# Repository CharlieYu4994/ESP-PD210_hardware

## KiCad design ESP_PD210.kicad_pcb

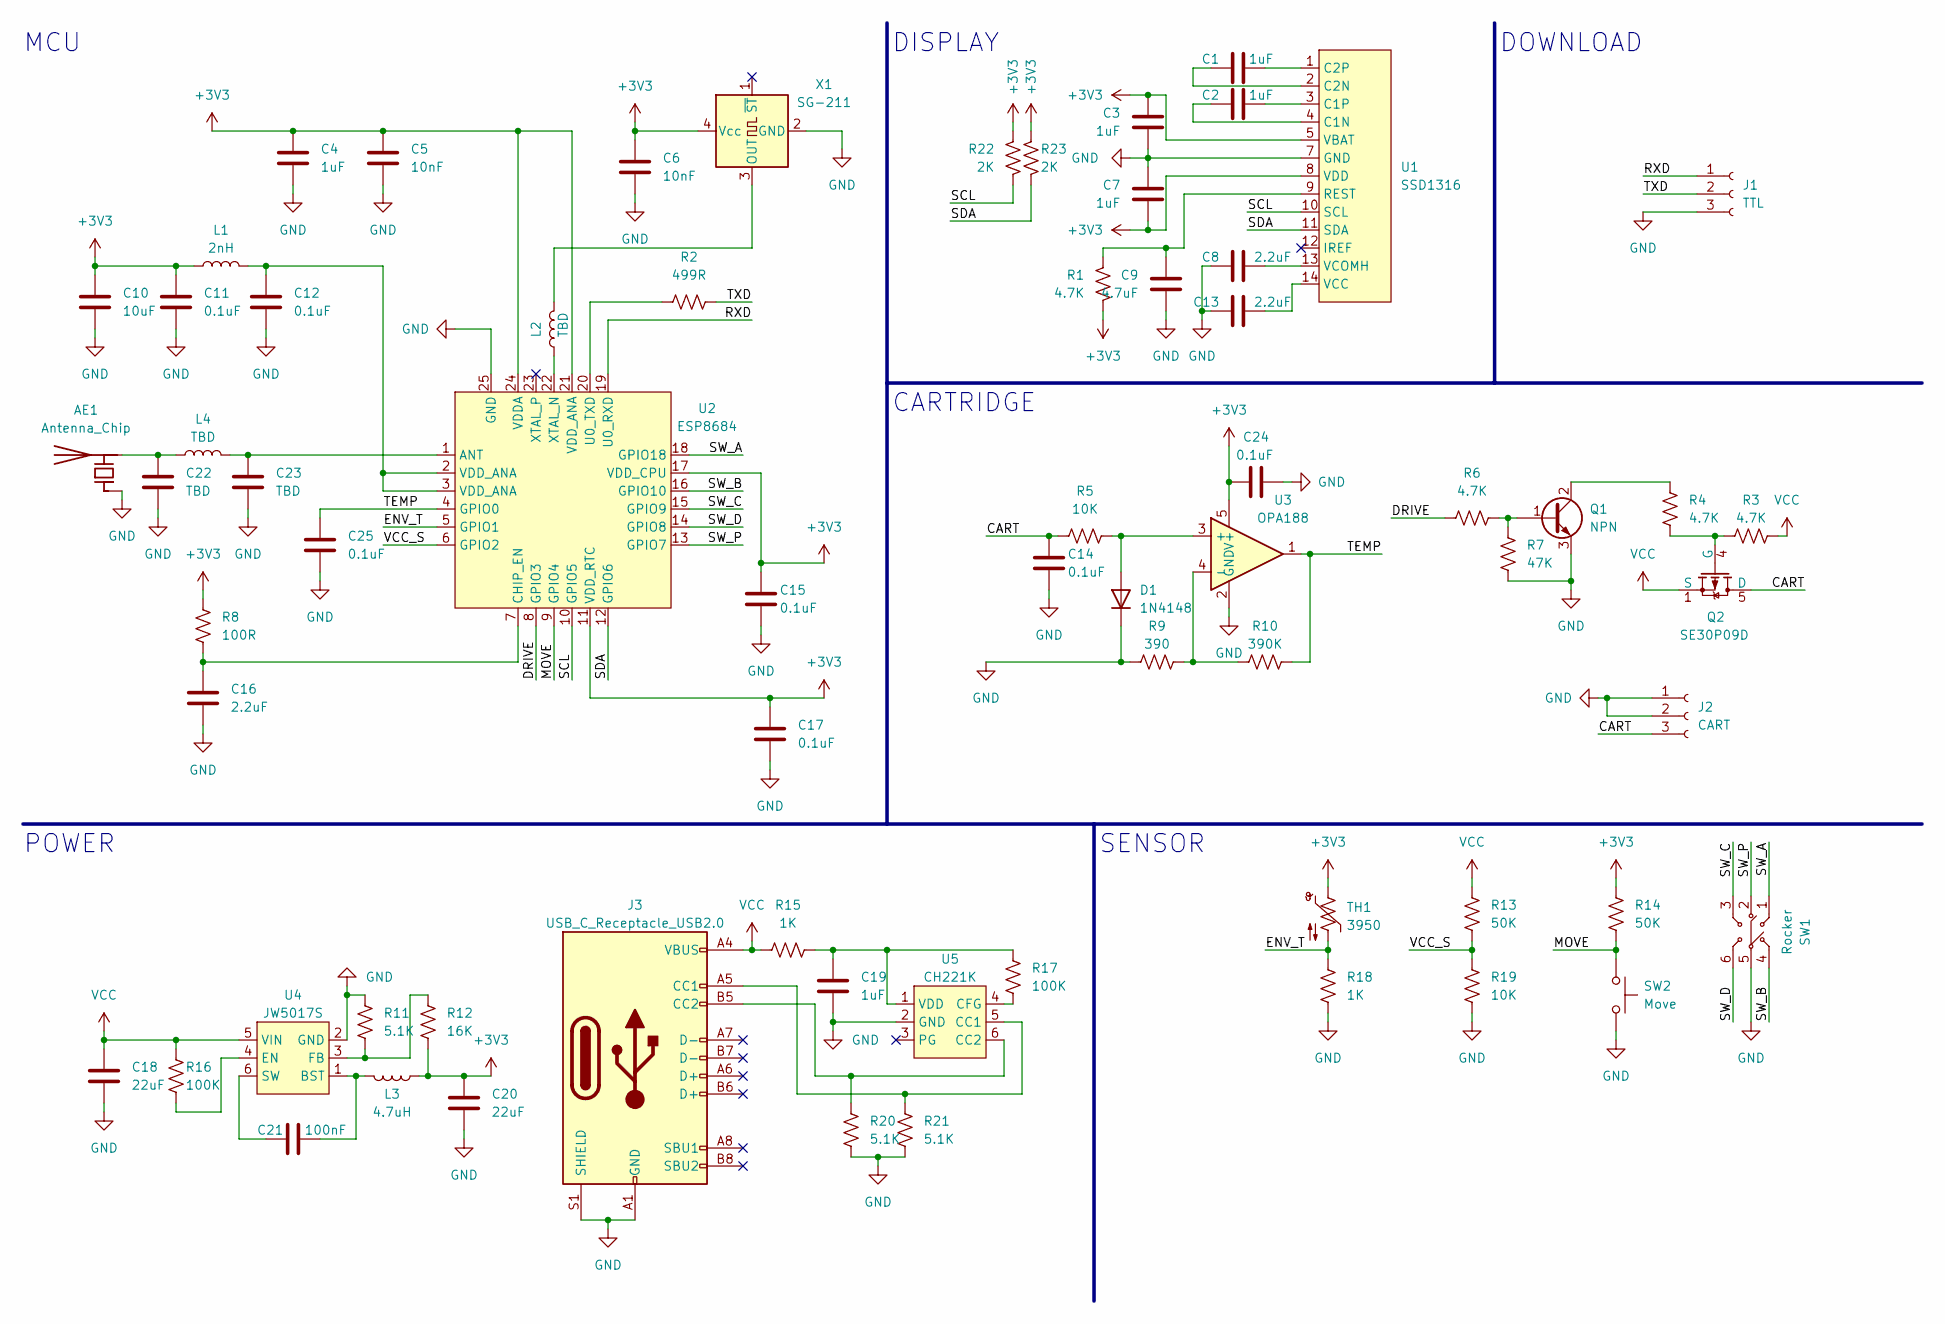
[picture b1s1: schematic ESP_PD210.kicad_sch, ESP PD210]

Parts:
AE1: Antenna_Chip; C01
C1, C2, C3, C4, C7, C19: 1uF; C_0402_1005Metric
C5, C6: 10nF; C_0402_1005Metric
C8, C13, C16: 2.2uF; C_0402_1005Metric
C9: 4.7uF; C_0402_1005Metric
C10: 10uF; C_0402_1005Metric
C11, C12, C14, C15, C17, C24, C25: 0.1uF; C_0402_1005Metric
C18, C20: 22uF; C_0402_1005Metric
C21: 100nF; C_0402_1005Metric
C22, C23: TBD; C_0402_1005Metric
D1: 1N4148; D_SOD-323
J1: TTL
J2: CART; JBC210
J3: USB_C_Receptacle_USB2.0; USB_C_Receptacle_HRO_TYPE-C-31-M-12
L1: 2nH; L_0402_1005Metric
L2, L4: TBD; L_0402_1005Metric
L3: 4.7uH; L_1008_2520Metric
Q1: NPN; SOT-23
Q2: SE30P09D; DFN-8-1EP_3x3mm_P0.5mm_EP1.66x2.38mm
R1, R3, R4, R6: 4.7K; R_0402_1005Metric
R2: 499R; R_0402_1005Metric
R5, R19: 10K; R_0402_1005Metric
R7: 47K; R_0402_1005Metric
R8: 100R; R_0402_1005Metric
R9: 390; R_0402_1005Metric
R10: 390K; R_0402_1005Metric
R11, R20, R21: 5.1K; R_0402_1005Metric
R12: 16K; R_0402_1005Metric
R13, R14: 50K; R_0402_1005Metric
R15, R18: 1K; R_0402_1005Metric
R16, R17: 100K; R_0402_1005Metric
R22, R23: 2K; R_0402_1005Metric
SW1: Rocker; 7*7*6-6P_WX
SW2: Move; X160
TH1: 3950; R_0603_1608Metric
U1: SSD1316; Display_FPC
U2: ESP8684; QFN-24-1EP_4x4mm_P0.5mm_EP2.7x2.7mm
U3: OPA188; SOT-23-5
U4: JW5017S; SOT-23-6
U5: CH221K; SOT-23-6
X1: SG-211; Oscillator_SMD_SeikoEpson_SG210-4Pin_2.5x2.0mm

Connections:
+3V3: C3.2, C4.1, C5.1, C6.1, C7.1, C10.1, C11.1, C15.1, C17.1, C20.1, C24.1, L1.1, L3.1, R1.1, R8.1, R12.1, R14.1, R22.2, R23.2, TH1.1, U1.5 (VBAT), U1.8 (VDD), U2.11 (VDD_RTC), U2.17 (VDD_CPU), U2.21 (VDD_ANA), U2.24 (VDDA), U3.5 (V+), X1.4 (Vcc)
/CART: C14.1, J2.3, Q2.5 (D), Q2.6 (D), Q2.7 (D), Q2.8 (D), Q2.9 (D), R5.1
/DRIVE: R6.1, U2.8 (GPIO3)
/ENV_T: R18.1, TH1.2, U2.5 (GPIO1)
/MOVE: R14.2, SW2.1, U2.9 (GPIO4)
/RXD: J1.1, U2.19 (U0_RXD)
/SCL: R22.1, U1.10 (SCL), U2.10 (GPIO5)
/SDA: R23.1, U1.11 (SDA), U2.12 (GPIO6)
/SW_A: SW1.1, U2.18 (GPIO18)
/SW_B: SW1.4, U2.16 (GPIO10)
/SW_C: SW1.3, U2.15 (GPIO9)
/SW_D: SW1.6, U2.14 (GPIO8)
/SW_P: SW1.2, U2.13 (GPIO7)
/TEMP: C25.1, R10.2, U2.4 (GPIO0), U3.1
/TXD: J1.2, R2.2
/VCC_S: R13.2, R19.1, U2.6 (GPIO2)
GND: AE1.1 (FEED), C3.1, C4.2, C5.2, C6.2, C7.2, C8.1, C9.1, C10.2, C11.2, C12.2, C13.1, C14.2, C15.2, C16.2, C17.2, C18.2, C19.2, C20.2, C22.2, C23.2, C24.2, C25.2, D1.1 (K), J1.3, J2.1, J2.2, J3.A1 (GND), J3.A12 (GND), J3.B1 (GND), J3.B12 (GND), J3.S1 (SHIELD), Q1.3 (E), R7.1, R9.1, R11.2, R18.2, R19.2, R20.2, R21.2, SW1.5, SW2.2, U1.7 (GND), U2.25 (GND), U3.2 (GND), U4.2 (GND), U5.2 (GND), X1.2 (GND)
unnamed: AE1.2 (PCB_Trace), C22.1, L4.1
unnamed: C1.1, U1.2 (C2N)
unnamed: C1.2, U1.1 (C2P)
unnamed: C2.1, U1.4 (C1N)
unnamed: C2.2, U1.3 (C1P)
unnamed: C8.2, U1.13 (VCOMH)
unnamed: C9.2, R1.2, U1.9 (REST)
unnamed: C12.1, L1.2, U2.2 (VDD_ANA), U2.3 (VDD_ANA)
unnamed: C13.2, U1.14 (VCC)
unnamed: C16.1, R8.2, U2.7 (CHIP_EN)
unnamed: C19.1, R15.1, R17.1, U5.1 (VDD)
unnamed: C21.1, U4.6 (SW)
unnamed: C21.2, L3.2, U4.1 (BST)
unnamed: C23.1, L4.2, U2.1 (ANT)
unnamed: D1.2 (A), R5.2, U3.3 (+)
unnamed: J3.A5 (CC1), R21.1, U5.5 (CC1)
unnamed: J3.B5 (CC2), R20.1, U5.6 (CC2)
unnamed: L2.1, U2.22 (XTAL_N)
unnamed: L2.2, X1.3 (OUT)
unnamed: Q1.1 (B), R6.2, R7.2
unnamed: Q1.2 (C), R4.1
unnamed: Q2.4 (G), R3.2, R4.2
unnamed: R2.1, U2.20 (U0_TXD)
unnamed: R9.2, R10.1, U3.4 (-)
unnamed: R11.1, R12.2, U4.3 (FB)
unnamed: R16.2, U4.4 (EN)
unnamed: R17.2, U5.4 (CFG)
VCC: C18.1, J3.A4 (VBUS), J3.A9 (VBUS), J3.B4 (VBUS), J3.B9 (VBUS), Q2.1 (S), Q2.2 (S), Q2.3 (S), R3.1, R13.1, R15.2, R16.1, U4.5 (VIN)

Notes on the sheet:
POWER
DOWNLOAD
DISPLAY
CARTRIDGE
SENSOR
MCU

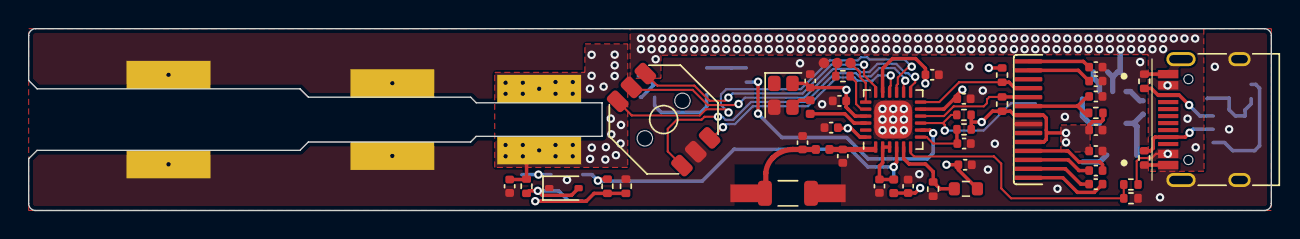
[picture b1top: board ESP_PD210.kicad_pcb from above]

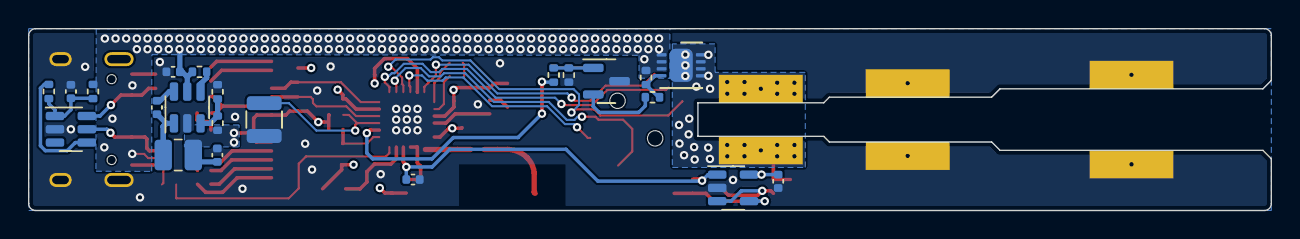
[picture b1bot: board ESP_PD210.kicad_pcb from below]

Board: 4 copper layers, 88.8 x 13.0 mm, 68 parts (22 on the bottom side), 45 nets.

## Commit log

2022-08-09 add files
2022-08-19 Replace the OPA with OPA188
2022-09-06 优化电源走线，增加 adc 处滤波电容
2022-09-06 Create LICENSE
2022-11-13 Optimize the layout
